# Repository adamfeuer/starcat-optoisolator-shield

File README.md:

StarCat Optoisolator Shield
===========================

This is an opto-isolated digital input/output shield for the Arduino Due.

It's good for low-noise synchronization of digital equipment (push-buttons, etc.) with 
an Arduino Due system. The optical isolation enables the connection of otherwise-noisy
external circuits or equipment, preventing ground or power supply noise from affecting 
sensitive ADC measurements. 

Meant for use with the [HackEEG](https://github.com/adamfeuer/hackeeg-shield) 24-bit EEG 
ADC board.

Features
========

* 4 opto-isolated inputs
* 2 opo-isolated outputs
* Screw terminals for connecting external inputs and outputs
* Uses Vishay [ILD213T](http://www.vishay.com/docs/83647/ild205t.pdf) optoisolator IC

License
=======

[Creative Commons By-Attribution ShareAlike 4.0](https://creativecommons.org/licenses/by-sa/4.0/)

Comments
========

If you have questions, comments, or improvements, I would love to know them!

cheers <br>
adam <br>
Adam Feuer <br>
Seattle, WA, USA <br>
adam@adamfeuer.com <br>
http://adamfeuer.com <br>

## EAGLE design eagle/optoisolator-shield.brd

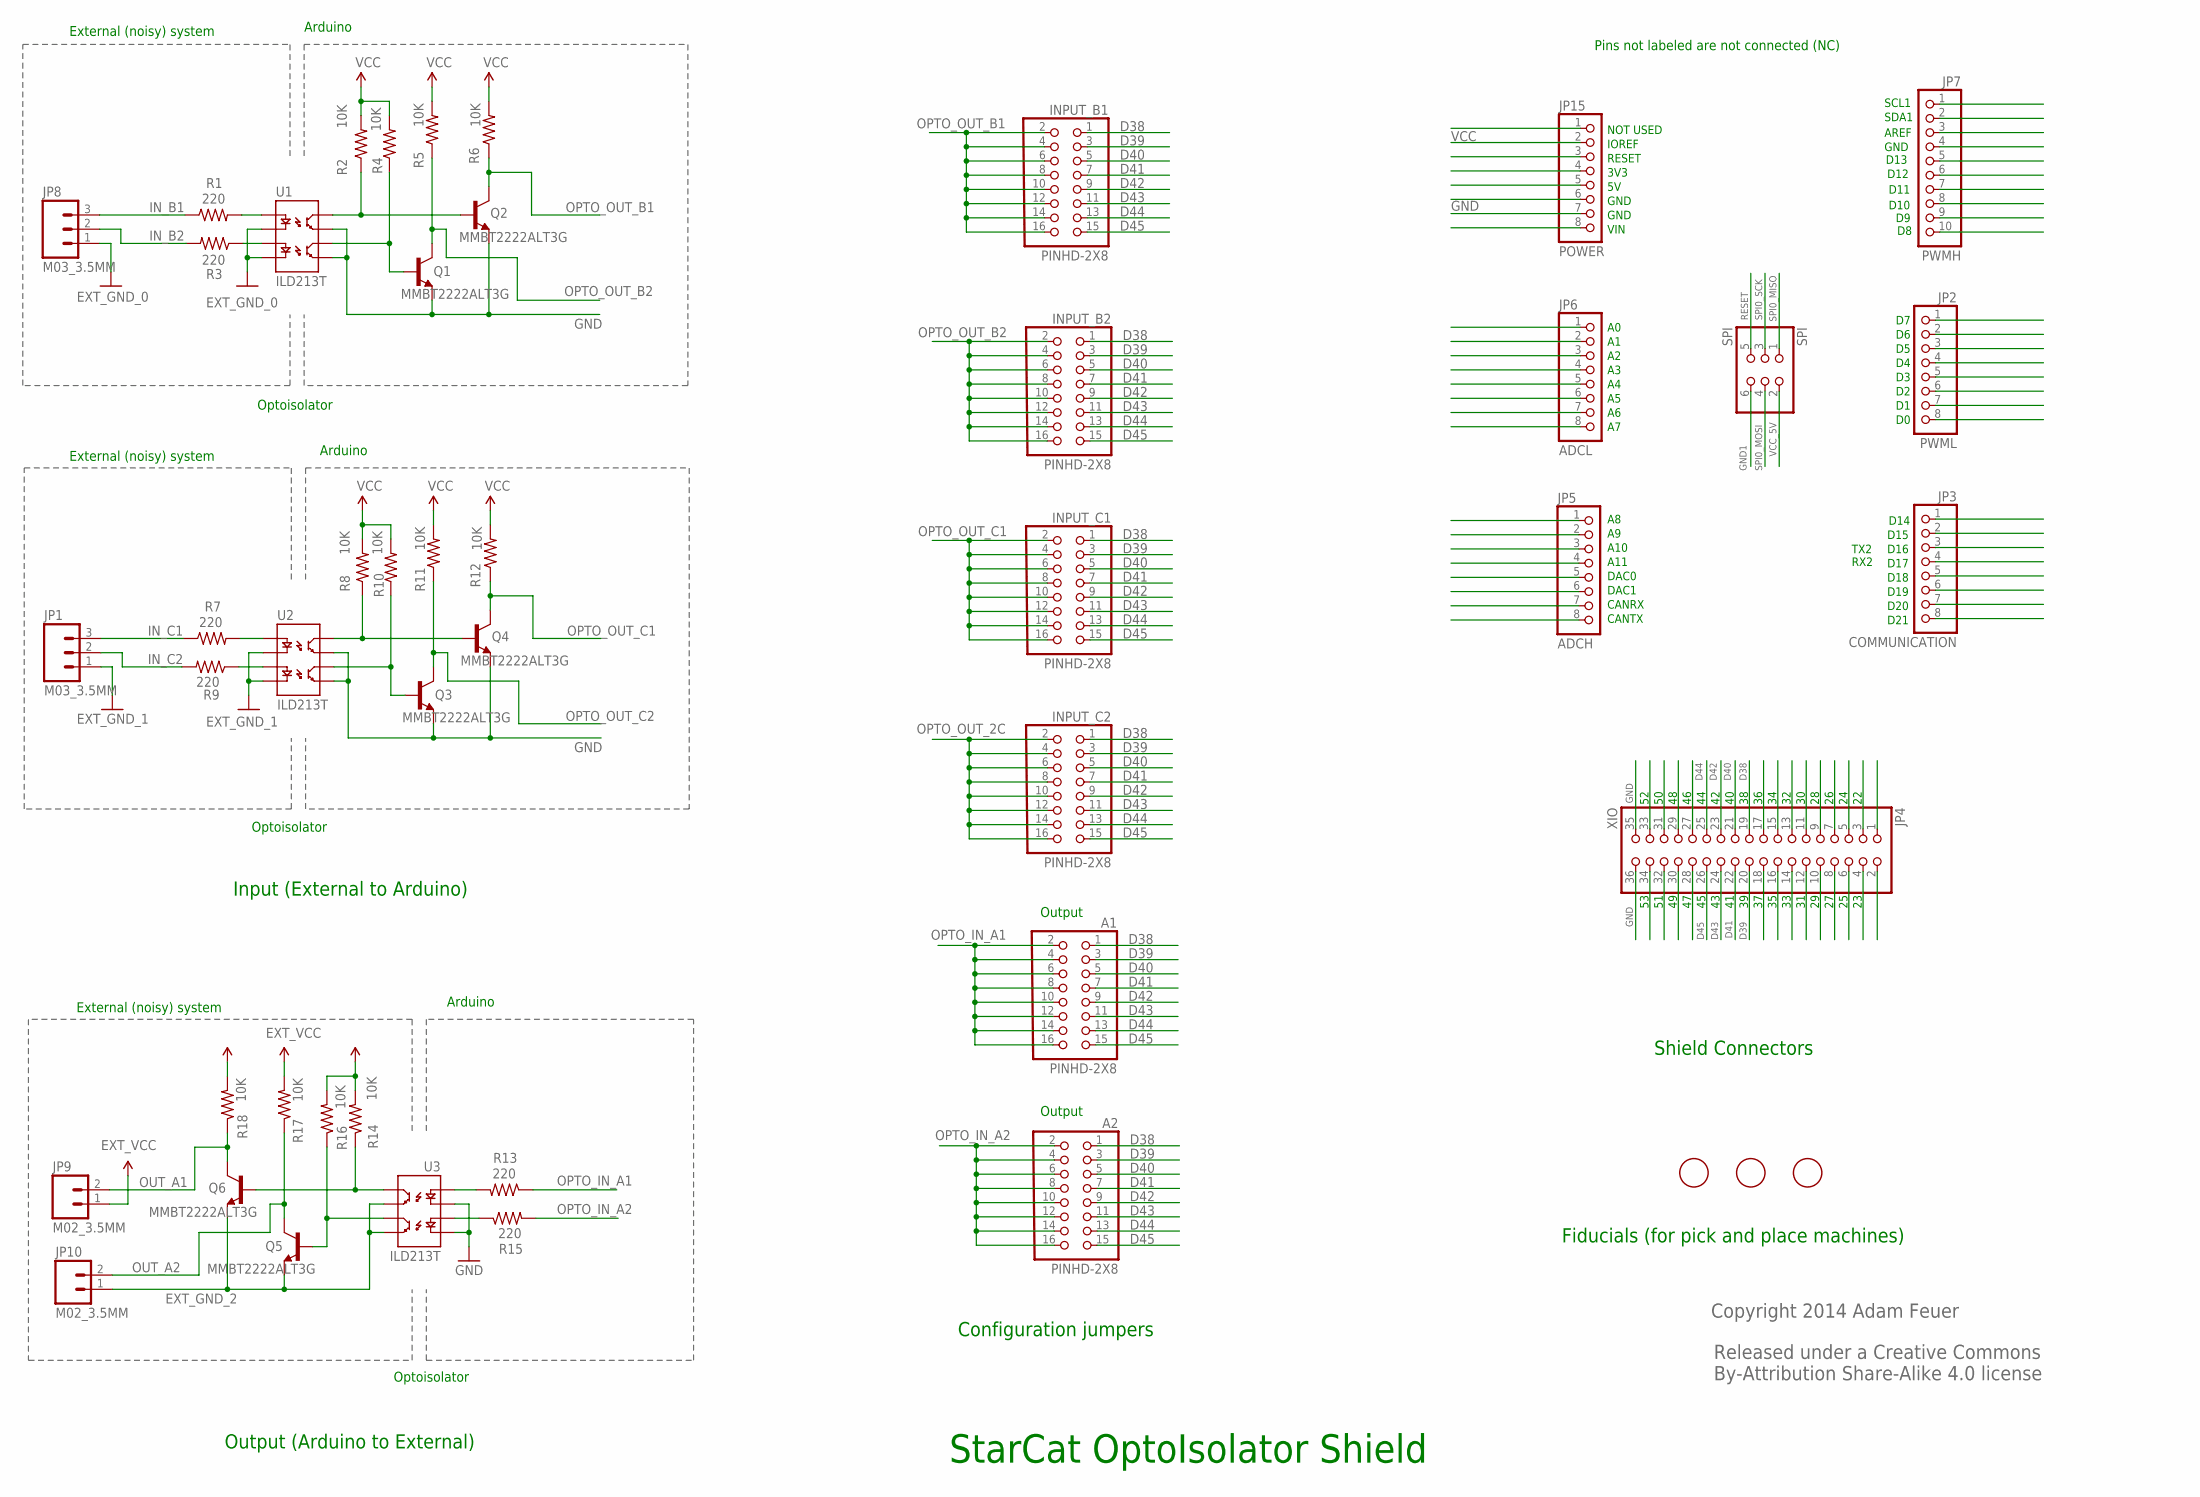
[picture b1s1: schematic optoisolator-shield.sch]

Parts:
A1, A2: PINHD-2X8; 2X08
INPUT_B1, INPUT_B2: PINHD-2X8; 2X08
INPUT_C1, INPUT_C2: PINHD-2X8; 2X08
JP1, JP8: M03_3.5MM; SCREWTERMINAL-3.5MM-3
JP2: PWML; 1X08
JP3: COMMUNICATION; 1X08
JP4: XIO; 2X18
JP5: ADCH; 1X08
JP6: ADCL; 1X08
JP7: PWMH; 1X10
JP9, JP10: M02_3.5MM; SCREWTERMINAL-3.5MM-2
JP15: POWER; 1X08
Q1, Q2, Q3, Q4, Q5, Q6: MMBT2222ALT3G; SOT23-3
R1, R3, R7, R9, R13, R15: 220; 0603-RES
R2, R4, R5, R6, R8, R10, R11, R12, R14, R16, R17, R18: 10K; 0603-RES
SPI: SPI; 2X03
U1, U2, U3: ILD213T; SO08-2
U$2, U$5, U$6: FIDUCIAL; FIDUCIAL_1MM

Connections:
D38: A1.1, A2.1, INPUT_B1.1, INPUT_B2.1, INPUT_C1.1, INPUT_C2.1, JP4.19
D39: A1.3, A2.3, INPUT_B1.3, INPUT_B2.3, INPUT_C1.3, INPUT_C2.3, JP4.20
D40: A1.5, A2.5, INPUT_B1.5, INPUT_B2.5, INPUT_C1.5, INPUT_C2.5, JP4.21
D41: A1.7, A2.7, INPUT_B1.7, INPUT_B2.7, INPUT_C1.7, INPUT_C2.7, JP4.22
D42: A1.9, A2.9, INPUT_B1.9, INPUT_B2.9, INPUT_C1.9, INPUT_C2.9, JP4.23
D43: A1.11, A2.11, INPUT_B1.11, INPUT_B2.11, INPUT_C1.11, INPUT_C2.11, JP4.24
D44: A1.13, A2.13, INPUT_B1.13, INPUT_B2.13, INPUT_C1.13, INPUT_C2.13, JP4.25
D45: A1.15, A2.15, INPUT_B1.15, INPUT_B2.15, INPUT_C1.15, INPUT_C2.15, JP4.26
EXT_GND_0: JP8.1, U1.2 (C1), U1.4 (C2)
EXT_GND_1: JP1.1, U2.2 (C1), U2.4 (C2)
EXT_GND_2: JP10.1, Q5.2 (E), Q6.2 (E), U3.5 (EM2), U3.7 (EM1)
EXT_VCC: JP9.1, R14.2, R16.2, R17.2, R18.2
GND: JP4.35, JP4.36, JP15.7, Q1.2 (E), Q2.2 (E), Q3.2 (E), Q4.2 (E), U1.5 (EM2), U1.7 (EM1), U2.5 (EM2), U2.7 (EM1), U3.2 (C1), U3.4 (C2)
GND1: SPI.6
IN_B1: JP8.3, R1.1
IN_B2: JP8.2, R3.2
IN_C1: JP1.3, R7.1
IN_C2: JP1.2, R9.2
unnamed: R1.2, U1.1 (A1)
unnamed: R3.1, U1.3 (A2)
unnamed: R7.2, U2.1 (A1)
unnamed: R9.1, U2.3 (A2)
unnamed: R13.2, U3.1 (A1)
unnamed: R15.1, U3.3 (A2)
OPTO_IN_A1: A1.2, A1.4, A1.6, A1.8, A1.10, A1.12, A1.14, A1.16, R13.1
OPTO_IN_A2: A2.2, A2.4, A2.6, A2.8, A2.10, A2.12, A2.14, A2.16, R15.2
OPTO_OUT_2C: INPUT_C2.2, INPUT_C2.4, INPUT_C2.6, INPUT_C2.8, INPUT_C2.10, INPUT_C2.12, INPUT_C2.14, INPUT_C2.16
OPTO_OUT_B1: INPUT_B1.2, INPUT_B1.4, INPUT_B1.6, INPUT_B1.8, INPUT_B1.10, INPUT_B1.12, INPUT_B1.14, INPUT_B1.16, Q2.3 (C), R6.1
OPTO_OUT_B2: INPUT_B2.2, INPUT_B2.4, INPUT_B2.6, INPUT_B2.8, INPUT_B2.10, INPUT_B2.12, INPUT_B2.14, INPUT_B2.16, Q1.3 (C), R5.1
OPTO_OUT_C1: INPUT_C1.2, INPUT_C1.4, INPUT_C1.6, INPUT_C1.8, INPUT_C1.10, INPUT_C1.12, INPUT_C1.14, INPUT_C1.16, Q4.3 (C), R12.1
OPTO_OUT_C2: Q3.3 (C), R11.1
OUT1N1: Q4.1 (B), R8.1, U2.8 (CL1)
OUT1N2: Q2.1 (B), R2.1, U1.8 (CL1)
OUT1N3: Q6.1 (B), R14.1, U3.8 (CL1)
OUT2N1: Q3.1 (B), R10.1, U2.6 (CL2)
OUT2N2: Q1.1 (B), R4.1, U1.6 (CL2)
OUT2N3: Q5.1 (B), R16.1, U3.6 (CL2)
OUT_A1: JP9.2, Q6.3 (C), R18.1
OUT_A2: JP10.2, Q5.3 (C), R17.1
RESET: SPI.5
SPI0_MISO: SPI.1
SPI0_MOSI: SPI.4
SPI0_SCK: SPI.3
VCC: JP15.2, R2.2, R4.2, R5.2, R6.2, R8.2, R10.2, R11.2, R12.2
VCC_5V: SPI.2

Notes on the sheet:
Configuration jumpers
Released under a Creative Commons By-Attribution Share-Alike 4.0 license
Copyright 2014 Adam Feuer
Shield Connectors
A10
A11
DAC0
DAC1
CANRX
CANTX
NOT USED
IOREF
RESET
3V3
GND
VIN
Fiducials (for pick and place machines)
Pins not labeled are not connected (NC)
Optoisolator
SCL1
SDA1
AREF
D13
D12
D11
D10
D14
D15
D16
D17
D18
D19
D20
D21
TX2
RX2
Arduino
External (noisy) system
Input (External to Arduino)
Output (Arduino to External)

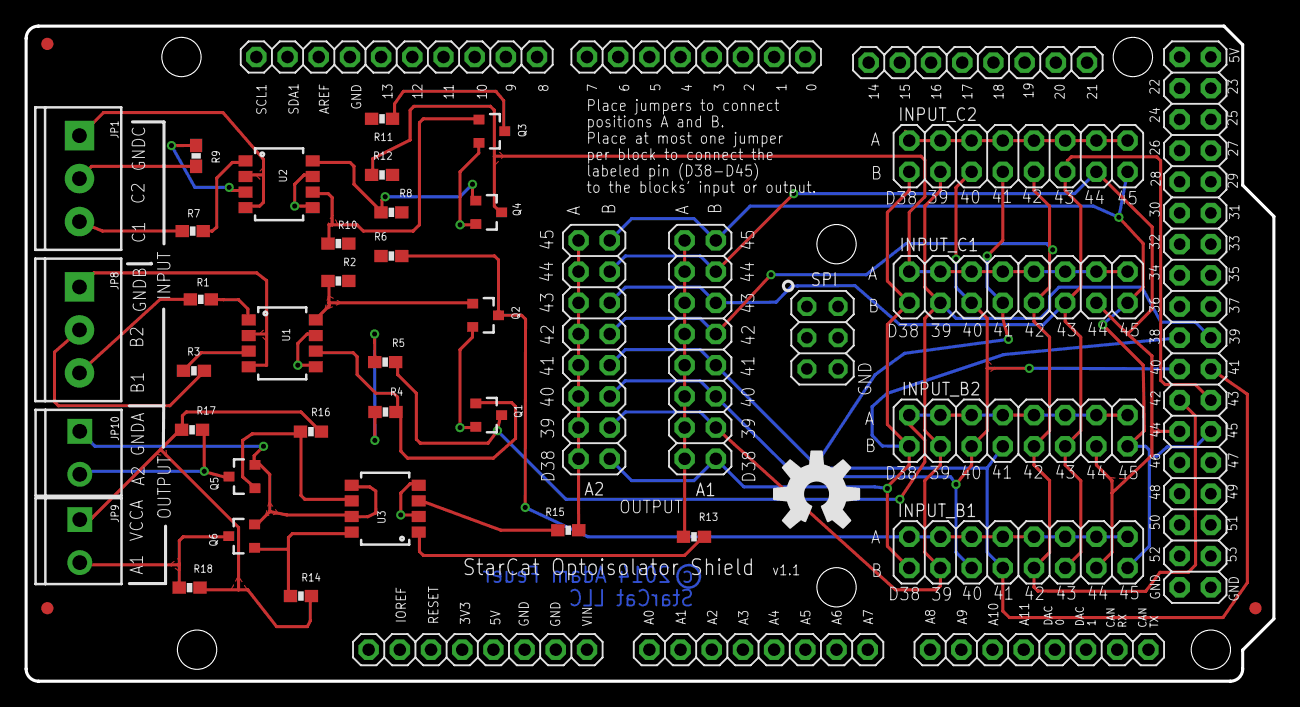
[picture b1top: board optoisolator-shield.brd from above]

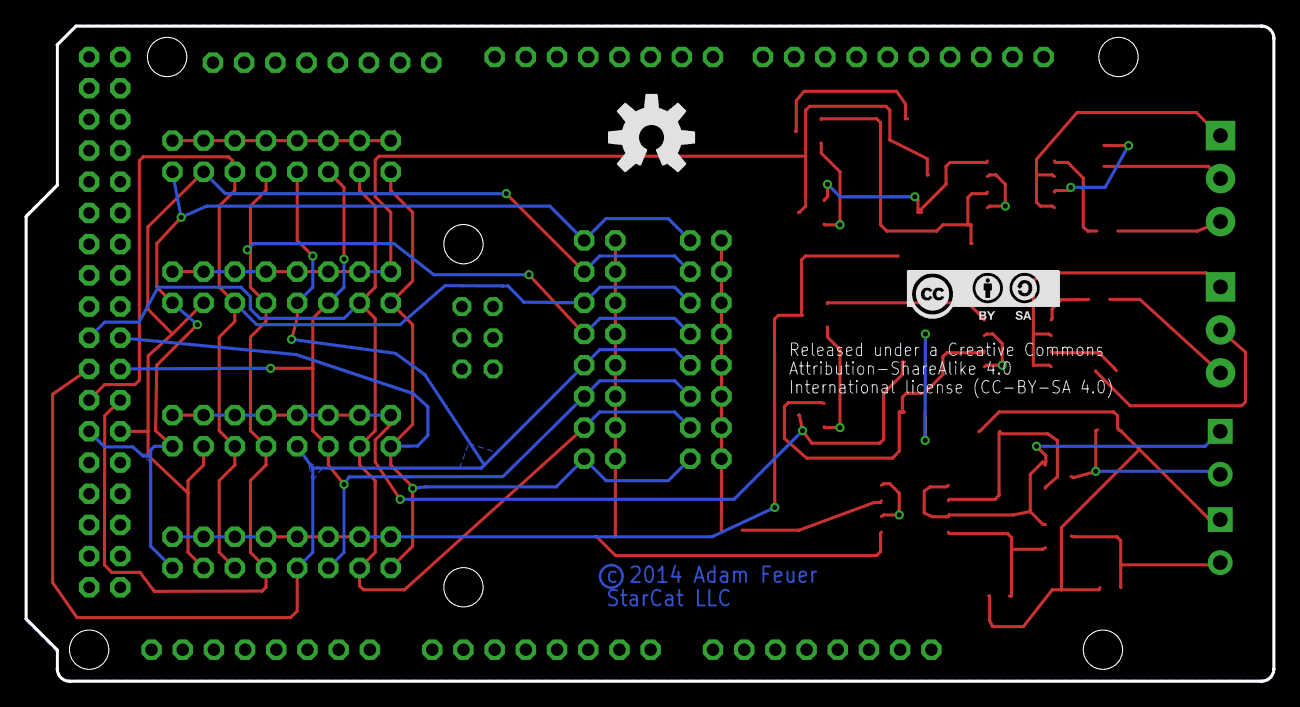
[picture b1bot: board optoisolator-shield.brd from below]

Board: 2 copper layers, 101.6 x 53.3 mm, 51 parts (2 on the bottom side), 39 nets.

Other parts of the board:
U$1, U$3: OSHW-LOGO-L
U$4: CC-BY-SA

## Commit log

2013-11-29 initial addition
2013-11-29 added optoisolators and config jumpers; jumpers are all connected to shield IO pins
2013-11-29 renamed shield files to match project name
2013-11-29 added headers library with 2x08 header
2013-12-01 fixed direction of optoisolators; added an output to go along with the 2 inputs; all components are still SMT
2013-12-02 added cam and util directories; routed board, touch-ups still in progress
2013-12-02 updated project name in packaging scripts
2013-12-03 updated board silkscreen to include instructions
2013-12-03 updated signal names for optoisolator in/out to match the board silkscreen labels
2013-12-04 corrected board outline positioning to make origin at 0,0; added creative-commons logo library
2013-12-04 removed unused layers from packaging scripts
2013-12-04 added schematic pdf
2013-12-04 added gerbv project file
2013-12-04 improved some trace clearances by rerouting them
2013-12-04 added optoisolator cam job
2013-12-04 improved some trace clearances
2014-01-13 correct layers in gerbv
2014-01-13 fixed XIO orientation error propagated from HackEEG shield
2014-01-22 updated silkscreen with correct dac0/1 and canrx/tx labels; updated fiducials so 2 share the same X and 2 share the same Y coordinates
2014-02-04 updated gerbv project
2014-02-04 added XIO connector labels to aid in debugging
2014-02-04 improved trace clearances; changed names of inputs from 1A... to A1... for better readability
2014-02-04 updated schematic renaming inputs/outputs 1A... to A1... for clarity
2014-02-04 improved trace clearance and copper pour
2014-12-07 added README, schematic, and PCB picture
2014-12-07 added LICENSE file
2014-12-07 added optoisolator-shield.pro
2014-12-07 added shield name to schematic
2014-12-07 updating layers
2014-12-07 rotating schematic PDF to be correct orientation
2014-12-07 wording clarification in README
2014-12-07 wording change in README

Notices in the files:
eagle/optoisolator-shield.brd:
International license (CC-BY-SA 4.0)
optoisolator-shield.sch:
By-Attribution Share-Alike 3.0 license
Copyright 2013 Adam Feuer
parts and their libraries:
SparkFun-Connectors: Licensing: CC v3.0 Share-Alike You are welcome to use this library for commercial purposes.
